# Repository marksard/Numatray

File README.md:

# Numatray
The Numatray is a 4-key macropad and fountain pen rest project.

# Completed example

# Layout

# Support software

QMK Firmware  
https://github.com/marksard/qmk_firmware/tree/own_build/keyboards/marksard/numatray

# Build guide

https://github.com/marksard/Numatray/blob/main/documents/buildguide.md

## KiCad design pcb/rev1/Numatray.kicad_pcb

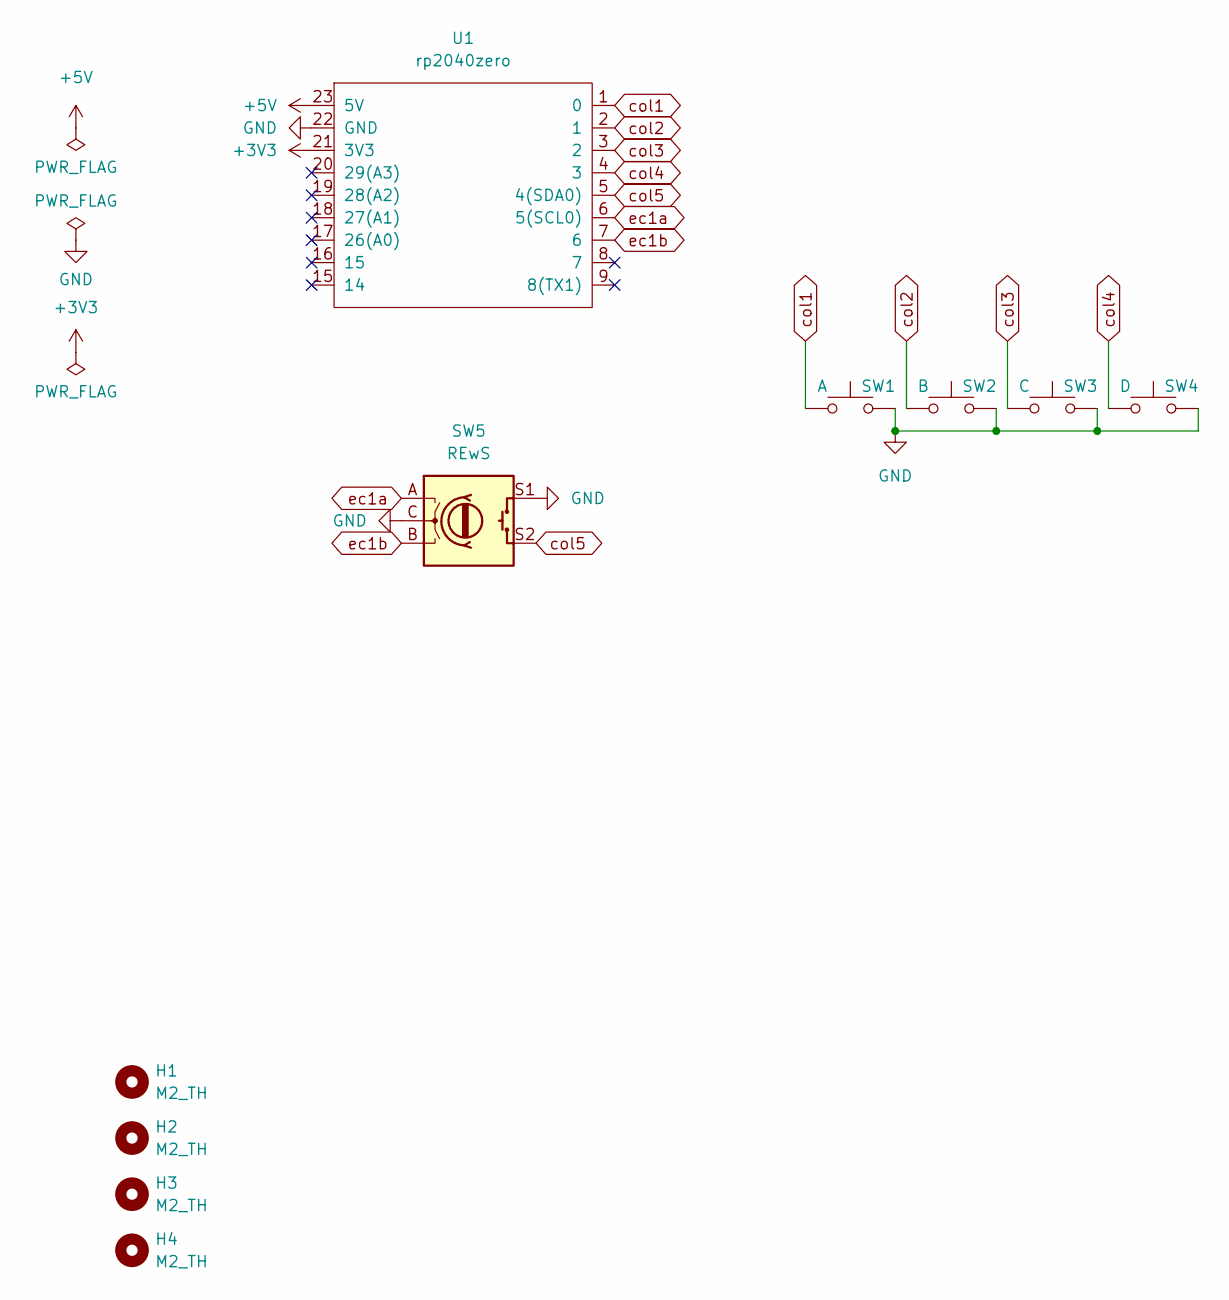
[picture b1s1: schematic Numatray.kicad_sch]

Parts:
H1, H2, H3, H4: M2_TH; M2_THT_Hole
SW1: A; MX-Solderable-1U; LCSC C5156480
SW2: B; MX-Solderable-1U; LCSC C5156480
SW3: C; MX-Solderable-1U; LCSC C5156480
SW4: D; MX-Solderable-1U; LCSC C5156480
SW5: REwS; RotaryEncoder_EC12E-Switch_Vertical
U1: rp2040zero; rp2040zero_compact

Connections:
+3V3: U1.21 (3V3)
+5V: U1.23 (5V)
GND: SW1.2, SW2.2, SW3.2, SW4.2, SW5.C, SW5.S1, U1.22 (GND)
col1: SW1.1, U1.1 (0)
col2: SW2.1, U1.2 (1)
col3: SW3.1, U1.3 (2)
col4: SW4.1, U1.4 (3)
col5: SW5.S2, U1.5 (4(SDA0))
ec1a: SW5.A, U1.6 (5(SCL0))
ec1b: SW5.B, U1.7 (6)

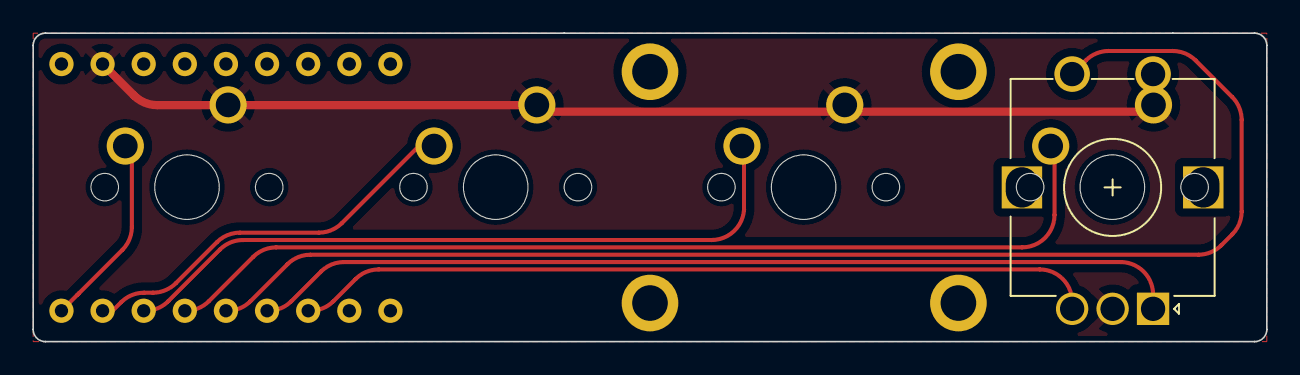
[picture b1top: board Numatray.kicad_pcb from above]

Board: 2 copper layers, 76.2 x 19.0 mm, 10 parts (1 on the bottom side), 8 nets.

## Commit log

2024-11-25 Create LICENSE
2024-11-25 Added PCB files
2025-01-31 add buildguide
